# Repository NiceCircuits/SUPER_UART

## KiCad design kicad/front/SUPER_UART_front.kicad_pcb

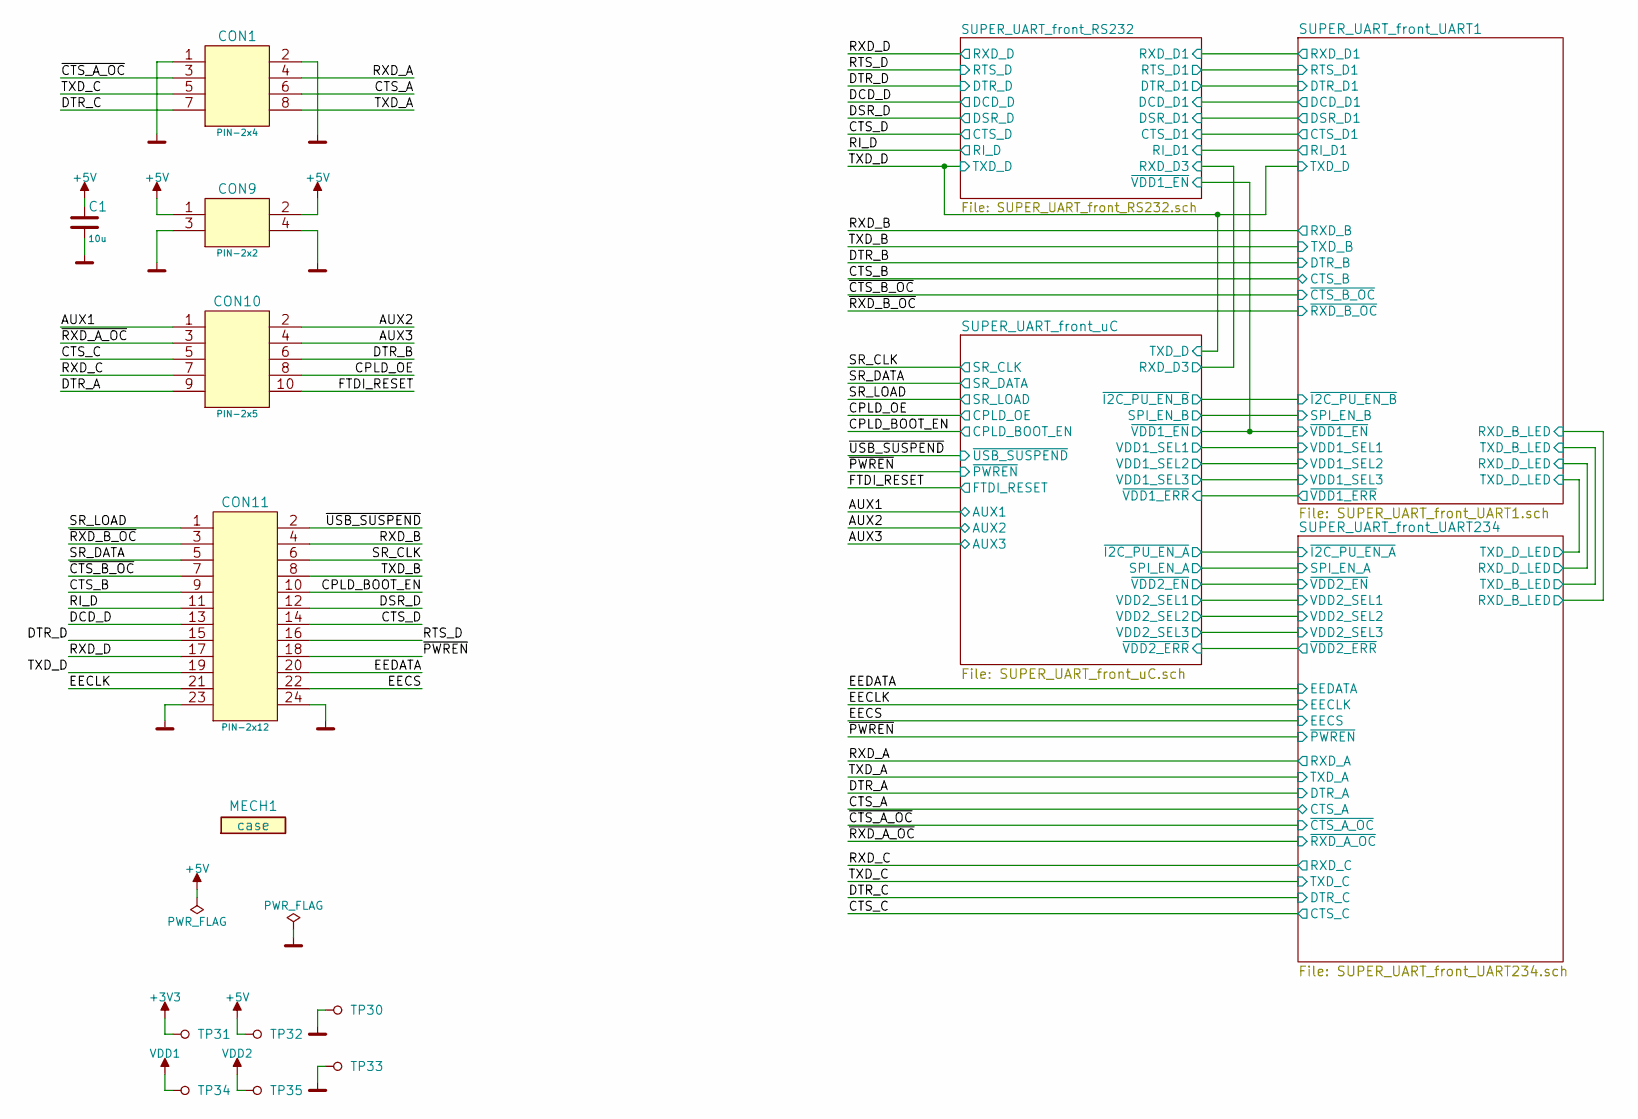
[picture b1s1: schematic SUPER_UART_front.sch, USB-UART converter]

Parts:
C1: 10u; 0805_N
CON1: PIN-2x4; PIN4x2SMD
CON9: PIN-2x2; PIN2x2SMD
CON10: PIN-2x5; PIN5x2SMD
CON11: PIN-2x12; PIN12x2SMD
MECH1: case; dummy
TP30, TP31, TP32, TP33, TP34, TP35: Testpoint; TP_1mm

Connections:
+3V3: TP31.1; also elsewhere on the board
+5V: C1.1, CON9.1, CON9.2, TP32.1; also elsewhere on the board
/AUX1: CON10.1; also elsewhere on the board
/AUX2: CON10.2; also elsewhere on the board
/AUX3: CON10.4; also elsewhere on the board
/CPLD_BOOT_EN: CON11.10; also elsewhere on the board
/CPLD_OE: CON10.8; also elsewhere on the board
/CTS_A: CON1.6; also elsewhere on the board
/CTS_B: CON11.9; also elsewhere on the board
/CTS_C: CON10.5; also elsewhere on the board
/CTS_D: CON11.14; also elsewhere on the board
/DCD_D: CON11.13; also elsewhere on the board
/DSR_D: CON11.12; also elsewhere on the board
/DTR_A: CON10.9; also elsewhere on the board
/DTR_B: CON10.6; also elsewhere on the board
/DTR_C: CON1.7; also elsewhere on the board
/DTR_D: CON11.15; also elsewhere on the board
/EECLK: CON11.21; also elsewhere on the board
/EECS: CON11.22; also elsewhere on the board
/EEDATA: CON11.20; also elsewhere on the board
/FTDI_RESET: CON10.10; also elsewhere on the board
/RI_D: CON11.11; also elsewhere on the board
/RTS_D: CON11.16; also elsewhere on the board
/RXD_A: CON1.4; also elsewhere on the board
/RXD_B: CON11.4; also elsewhere on the board
/RXD_C: CON10.7; also elsewhere on the board
/RXD_D: CON11.17; also elsewhere on the board
/SR_CLK: CON11.6; also elsewhere on the board
/SR_DATA: CON11.5; also elsewhere on the board
/SR_LOAD: CON11.1; also elsewhere on the board
/TXD_A: CON1.8; also elsewhere on the board
/TXD_B: CON11.8; also elsewhere on the board
/TXD_C: CON1.5; also elsewhere on the board
/TXD_D: CON11.19; also elsewhere on the board
/~CTS_A_OC: CON1.3; also elsewhere on the board
/~CTS_B_OC: CON11.7; also elsewhere on the board
/~PWREN: CON11.18; also elsewhere on the board
/~RXD_A_OC: CON10.3; also elsewhere on the board
/~RXD_B_OC: CON11.3; also elsewhere on the board
/~USB_SUSPEND: CON11.2; also elsewhere on the board
GND: C1.2, CON1.1, CON1.2, CON9.3, CON9.4, CON11.23, CON11.24, TP30.1, TP33.1; also elsewhere on the board
VDD1: TP34.1; also elsewhere on the board
VDD2: TP35.1; also elsewhere on the board

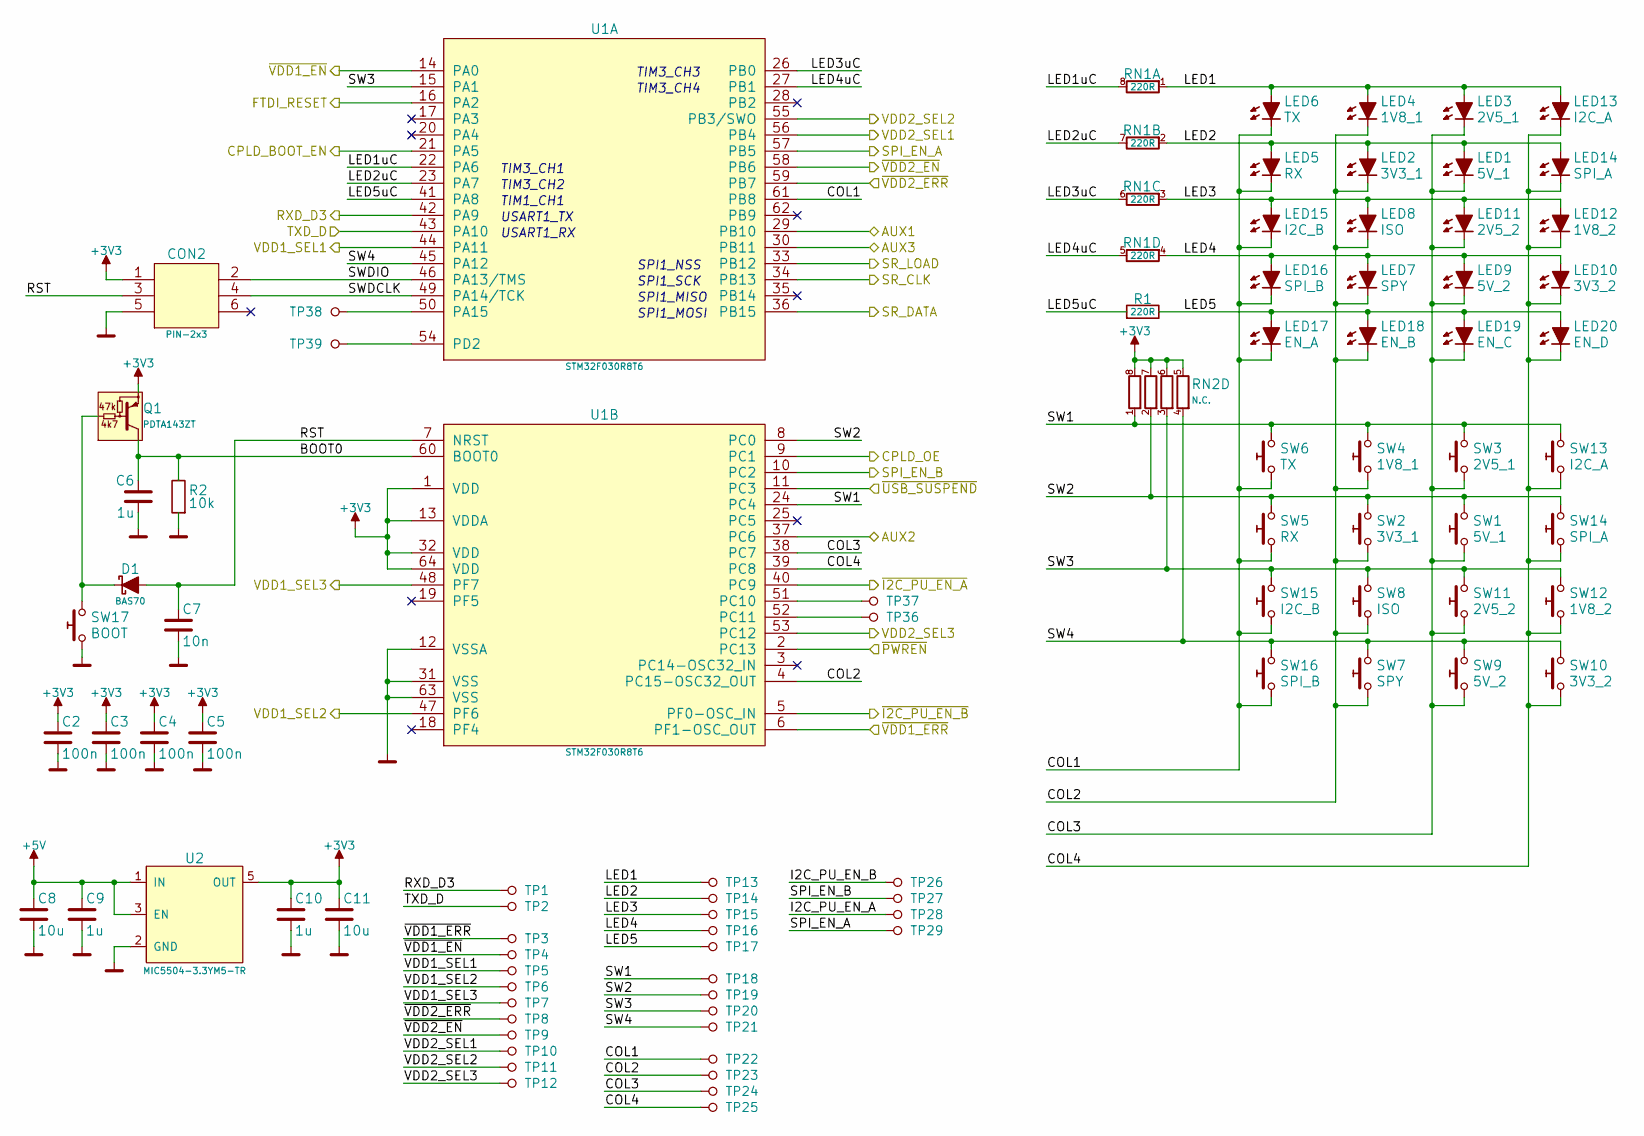
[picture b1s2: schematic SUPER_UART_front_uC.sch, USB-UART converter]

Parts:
C2, C3, C4, C5: 100n; 0603_N
C6, C9, C10: 1u; 0603_N
C7: 10n; 0603_N
C8, C11: 10u; 0805_N
CON2: PIN-2x3; PIN3x2SMD
D1: BAS70; SOT23-3_N
LED1: 5V_1; 0805D
LED2: 3V3_1; 0805D
LED3: 2V5_1; 0805D
LED4: 1V8_1; 0805D
LED5: RX; 0805D
LED6: TX; 0805D
LED7: SPY; 0805D
LED8: ISO; 0805D
LED9: 5V_2; 0805D
LED10: 3V3_2; 0805D
LED11: 2V5_2; 0805D
LED12: 1V8_2; 0805D
LED13: I2C_A; 0805D
LED14: SPI_A; 0805D
LED15: I2C_B; 0805D
LED16: SPI_B; 0805D
LED17: EN_A; 0805D
LED18: EN_B; 0805D
LED19: EN_C; 0805D
LED20: EN_D; 0805D
Q1: PDTA143ZT; SOT23-3_N
R1: 220R; 0603_R_N
R2: 10k; 0603_R_N
RN1: 220R; 4x0603_N
RN2: N.C.; 4x0603_N
SW1: 5V_1; TACTB-64K-F
SW2: 3V3_1; TACTB-64K-F
SW3: 2V5_1; TACTB-64K-F
SW4: 1V8_1; TACTB-64K-F
SW5: RX; TACTB-64K-F
SW6: TX; TACTB-64K-F
SW7: SPY; TACTB-64K-F
SW8: ISO; TACTB-64K-F
SW9: 5V_2; TACTB-64K-F
SW10: 3V3_2; TACTB-64K-F
SW11: 2V5_2; TACTB-64K-F
SW12: 1V8_2; TACTB-64K-F
SW13: I2C_A; TACTB-64K-F
SW14: SPI_A; TACTB-64K-F
SW15: I2C_B; TACTB-64K-F
SW16: SPI_B; TACTB-64K-F
SW17: BOOT; TACTB-64K-F
TP1, TP2, TP3, TP4, TP5, TP6, TP7, TP8, TP9, TP10, TP11, TP12, TP13, TP14, TP15, TP16, TP17, TP18, TP19, TP20, TP21, TP22, TP23, TP24, TP25, TP26, TP27, TP28, TP29, TP36, TP37, TP38, TP39: Testpoint; TP_1mm
U1: STM32F030R8T6; QFP-64-0.5_N
U2: MIC5504-3.3YM5-TR; SOT23-5_N

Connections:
+3V3: C2.1, C3.1, C4.1, C5.1, C10.1, C11.1, CON2.1, Q1.2 (E), RN2.5, RN2.6, RN2.7, RN2.8, U1.1 (VDD), U1.13 (VDDA), U1.32 (VDD), U1.64 (VDD), U2.5 (OUT); also elsewhere on the board
+5V: C8.1, C9.1, U2.1 (IN), U2.3 (EN); also elsewhere on the board
/AUX1: U1.29 (PB10); also elsewhere on the board
/AUX2: U1.37 (PC6); also elsewhere on the board
/AUX3: U1.30 (PB11); also elsewhere on the board
/CPLD_BOOT_EN: U1.21 (PA5); also elsewhere on the board
/CPLD_OE: U1.9 (PC1); also elsewhere on the board
/FTDI_RESET: U1.16 (PA2); also elsewhere on the board
/SR_CLK: U1.34 (PB13); also elsewhere on the board
/SR_DATA: U1.36 (PB15); also elsewhere on the board
/SR_LOAD: U1.33 (PB12); also elsewhere on the board
/SUPER_UART_front_RS232/RXD_D3: TP1.1, U1.42 (PA9); also elsewhere on the board
/SUPER_UART_front_RS232/~VDD1_EN: TP4.1, U1.14 (PA0); also elsewhere on the board
/SUPER_UART_front_UART1/I2C_PU_EN_B: TP26.1, U1.5 (PF0-OSC_IN); also elsewhere on the board
/SUPER_UART_front_UART1/SPI_EN_B: TP27.1, U1.10 (PC2); also elsewhere on the board
/SUPER_UART_front_UART1/VDD1_SEL1: TP5.1, U1.44 (PA11); also elsewhere on the board
/SUPER_UART_front_UART1/VDD1_SEL2: TP6.1, U1.47 (PF6); also elsewhere on the board
/SUPER_UART_front_UART1/VDD1_SEL3: TP7.1, U1.48 (PF7); also elsewhere on the board
/SUPER_UART_front_UART1/~VDD1_ERR: TP3.1, U1.6 (PF1-OSC_OUT); also elsewhere on the board
/SUPER_UART_front_UART234/I2C_PU_EN_A: TP28.1, U1.40 (PC9); also elsewhere on the board
/SUPER_UART_front_UART234/SPI_EN_A: TP29.1, U1.57 (PB5); also elsewhere on the board
/SUPER_UART_front_UART234/VDD2_SEL1: TP10.1, U1.56 (PB4); also elsewhere on the board
/SUPER_UART_front_UART234/VDD2_SEL2: TP11.1, U1.55 (PB3/SWO); also elsewhere on the board
/SUPER_UART_front_UART234/VDD2_SEL3: TP12.1, U1.53 (PC12); also elsewhere on the board
/SUPER_UART_front_UART234/~VDD2_EN: TP9.1, U1.58 (PB6); also elsewhere on the board
/SUPER_UART_front_UART234/~VDD2_ERR: TP8.1, U1.59 (PB7); also elsewhere on the board
/SUPER_UART_front_uC/BOOT0: C6.1, Q1.3 (C), R2.2, U1.60 (BOOT0)
/SUPER_UART_front_uC/COL1: LED5.1 (A), LED6.1 (A), LED15.1 (A), LED16.1 (A), LED17.1 (A), SW5.2, SW6.2, SW15.2, SW16.2, TP22.1, U1.61 (PB8)
/SUPER_UART_front_uC/COL2: LED2.1 (A), LED4.1 (A), LED7.1 (A), LED8.1 (A), LED18.1 (A), SW2.2, SW4.2, SW7.2, SW8.2, TP23.1, U1.4 (PC15-OSC32_OUT)
/SUPER_UART_front_uC/COL3: LED1.1 (A), LED3.1 (A), LED9.1 (A), LED11.1 (A), LED19.1 (A), SW1.2, SW3.2, SW9.2, SW11.2, TP24.1, U1.38 (PC7)
/SUPER_UART_front_uC/COL4: LED10.1 (A), LED12.1 (A), LED13.1 (A), LED14.1 (A), LED20.1 (A), SW10.2, SW12.2, SW13.2, SW14.2, TP25.1, U1.39 (PC8)
/SUPER_UART_front_uC/LED1: LED3.2 (C), LED4.2 (C), LED6.2 (C), LED13.2 (C), RN1.1, TP13.1
/SUPER_UART_front_uC/LED1uC: RN1.8, U1.22 (PA6)
/SUPER_UART_front_uC/LED2: LED1.2 (C), LED2.2 (C), LED5.2 (C), LED14.2 (C), RN1.2, TP14.1
/SUPER_UART_front_uC/LED2uC: RN1.7, U1.23 (PA7)
/SUPER_UART_front_uC/LED3: LED8.2 (C), LED11.2 (C), LED12.2 (C), LED15.2 (C), RN1.3, TP15.1
/SUPER_UART_front_uC/LED3uC: RN1.6, U1.26 (PB0)
/SUPER_UART_front_uC/LED4: LED7.2 (C), LED9.2 (C), LED10.2 (C), LED16.2 (C), RN1.4, TP16.1
/SUPER_UART_front_uC/LED4uC: RN1.5, U1.27 (PB1)
/SUPER_UART_front_uC/LED5: LED17.2 (C), LED18.2 (C), LED19.2 (C), LED20.2 (C), R1.2, TP17.1
/SUPER_UART_front_uC/LED5uC: R1.1, U1.41 (PA8)
/SUPER_UART_front_uC/RST: C7.1, CON2.3, D1.1 (C), U1.7 (NRST)
/SUPER_UART_front_uC/SW1: RN2.1, SW3.1, SW4.1, SW6.1, SW13.1, TP18.1, U1.24 (PC4)
/SUPER_UART_front_uC/SW2: RN2.2, SW1.1, SW2.1, SW5.1, SW14.1, TP19.1, U1.8 (PC0)
/SUPER_UART_front_uC/SW3: RN2.3, SW8.1, SW11.1, SW12.1, SW15.1, TP20.1, U1.15 (PA1)
/SUPER_UART_front_uC/SW4: RN2.4, SW7.1, SW9.1, SW10.1, SW16.1, TP21.1, U1.45 (PA12)
/SUPER_UART_front_uC/SWDCLK: CON2.4, U1.49 (PA14/TCK)
/SUPER_UART_front_uC/SWDIO: CON2.2, U1.46 (PA13/TMS)
/TXD_D: TP2.1, U1.43 (PA10); also elsewhere on the board
/~PWREN: U1.2 (PC13); also elsewhere on the board
/~USB_SUSPEND: U1.11 (PC3); also elsewhere on the board
GND: C2.2, C3.2, C4.2, C5.2, C6.2, C7.2, C8.2, C9.2, C10.2, C11.2, CON2.5, R2.1, SW17.2, U1.12 (VSSA), U1.31 (VSS), U1.63 (VSS), U2.2 (GND); also elsewhere on the board
unnamed: D1.3 (A), Q1.1 (B), SW17.1
unnamed: TP36.1, U1.52 (PC11)
unnamed: TP37.1, U1.51 (PC10)
unnamed: TP38.1, U1.50 (PA15)
unnamed: TP39.1, U1.54 (PD2)

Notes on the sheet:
USART1_TX
USART1_RX
TIM3_CH1
TIM3_CH2
TIM1_CH1
TIM3_CH3
TIM3_CH4
SPI1_NSS
SPI1_SCK
SPI1_MISO
SPI1_MOSI

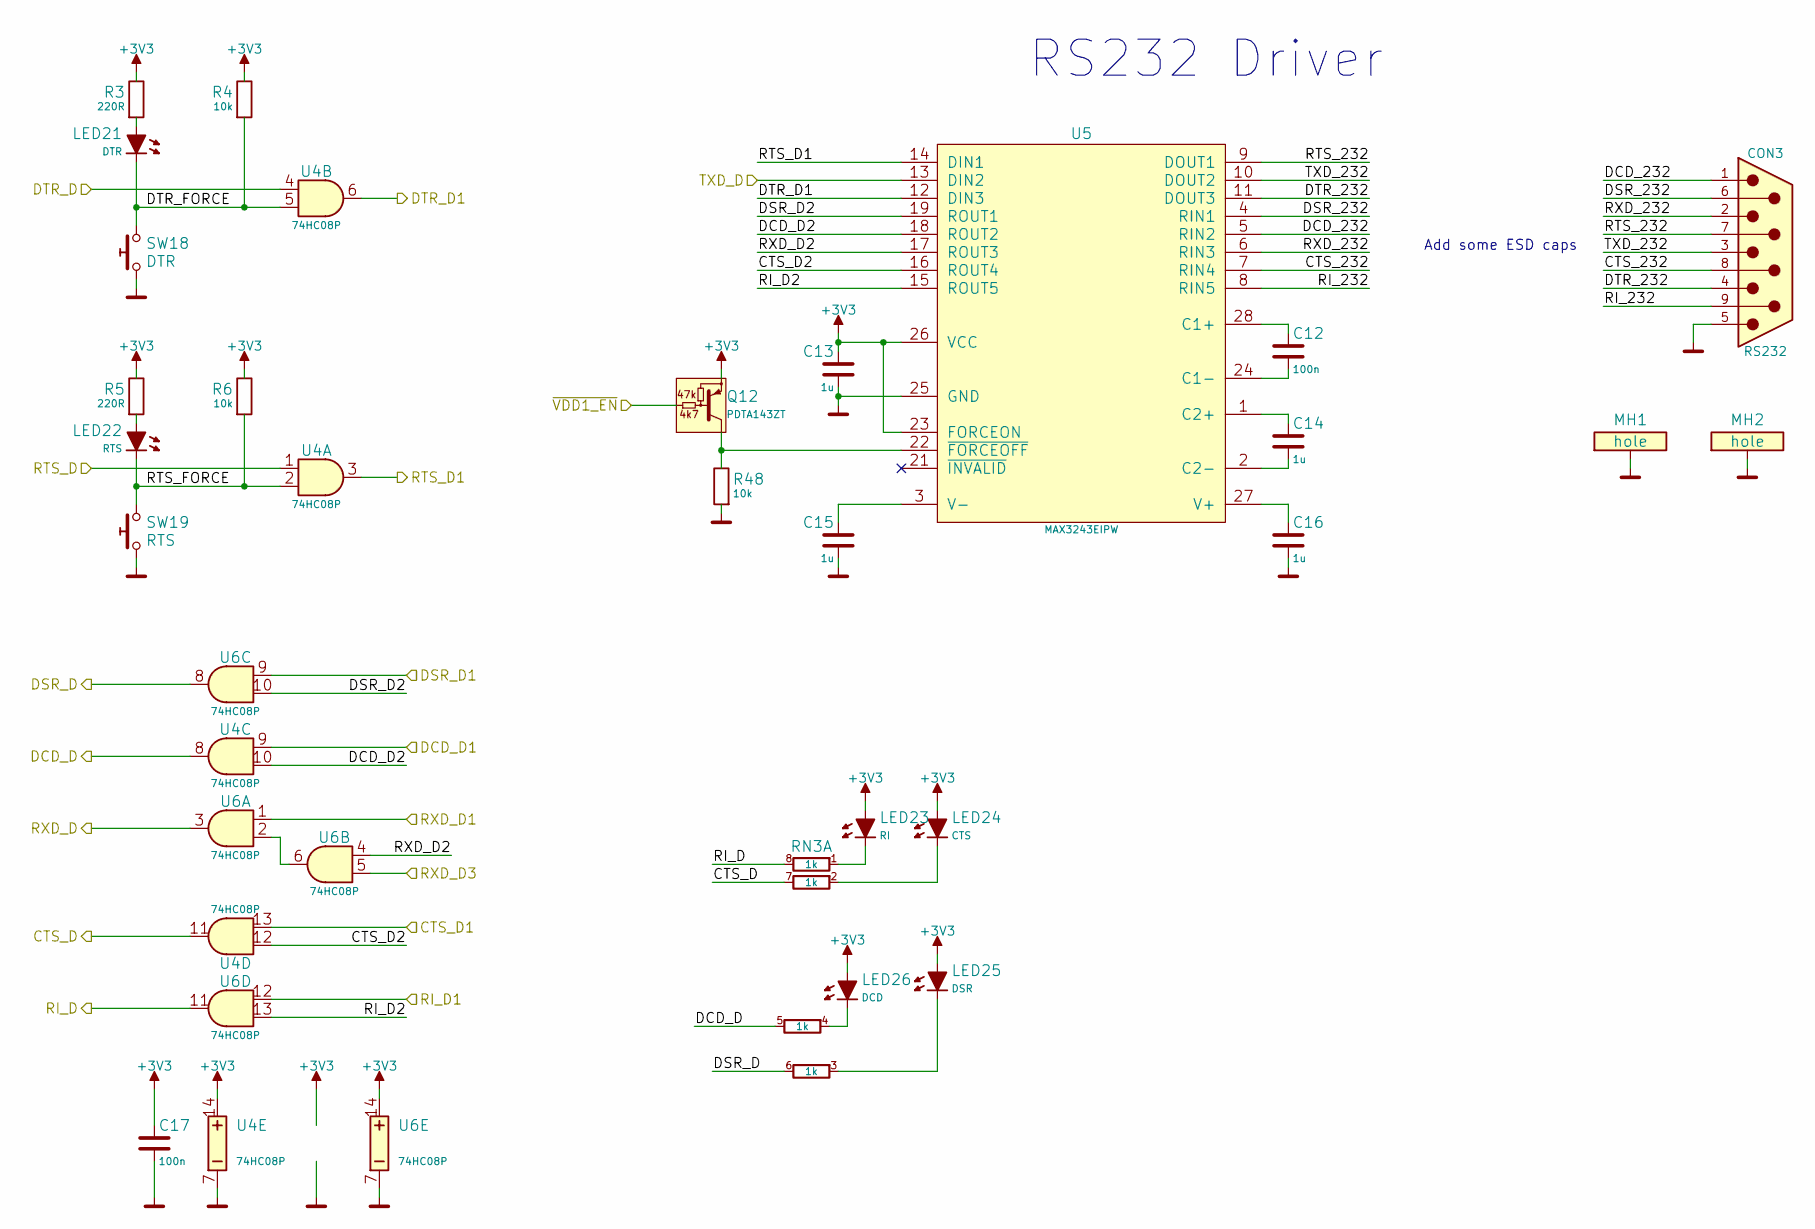
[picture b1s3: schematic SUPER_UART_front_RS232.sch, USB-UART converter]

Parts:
C12, C17: 100n; 0603_N
C13, C14, C15, C16: 1u; 0603_N
CON3: RS232; DB9MV
LED21: DTR; 0805D
LED22: RTS; 0805D
LED23: RI; 0805D
LED24: CTS; 0805D
LED25: DSR; 0805D
LED26: DCD; 0805D
MH1, MH2: hole; mounting_hole_3.2_7.5_plated
Q12: PDTA143ZT; SOT23-3_N
R3, R5: 220R; 0603_R_N
R4, R6, R48: 10k; 0603_R_N
RN3: 1k; 4x0603_N
SW18: DTR; TACTB-64K-F
SW19: RTS; TACTB-64K-F
U4, U6: 74HC08P; TSSOP-14_N
U5: MAX3243EIPW; TSSOP-28_N

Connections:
+3V3: C13.1, C17.1, LED23.2 (C), LED24.2 (C), LED25.2 (C), LED26.2 (C), Q12.2 (E), R3.2, R4.2, R5.2, R6.2, U4.14 (VCC), U5.23 (FORCEON), U5.26 (VCC), U6.14 (VCC); also elsewhere on the board
/CTS_D: RN3.7, U4.11 (OUT); also elsewhere on the board
/DCD_D: RN3.5, U4.8 (OUT); also elsewhere on the board
/DSR_D: RN3.6, U6.8 (OUT); also elsewhere on the board
/DTR_D: U4.4 (in1); also elsewhere on the board
/RI_D: RN3.8, U6.11 (OUT); also elsewhere on the board
/RTS_D: U4.1 (in1); also elsewhere on the board
/RXD_D: U6.3 (OUT); also elsewhere on the board
/SUPER_UART_front_RS232/CTS_232: CON3.8, U5.7 (RIN4)
/SUPER_UART_front_RS232/CTS_D1: U4.13 (in2); also elsewhere on the board
/SUPER_UART_front_RS232/CTS_D2: U4.12 (in1), U5.16 (ROUT4)
/SUPER_UART_front_RS232/DCD_232: CON3.1, U5.5 (RIN2)
/SUPER_UART_front_RS232/DCD_D1: U4.9 (in1); also elsewhere on the board
/SUPER_UART_front_RS232/DCD_D2: U4.10 (in2), U5.18 (ROUT2)
/SUPER_UART_front_RS232/DSR_232: CON3.6, U5.4 (RIN1)
/SUPER_UART_front_RS232/DSR_D1: U6.9 (in1); also elsewhere on the board
/SUPER_UART_front_RS232/DSR_D2: U5.19 (ROUT1), U6.10 (in2)
/SUPER_UART_front_RS232/DTR_232: CON3.4, U5.11 (DOUT3)
/SUPER_UART_front_RS232/DTR_D1: U4.6 (OUT), U5.12 (DIN3); also elsewhere on the board
/SUPER_UART_front_RS232/DTR_FORCE: LED21.1 (A), R4.1, SW18.1, U4.5 (in2)
/SUPER_UART_front_RS232/RI_232: CON3.9, U5.8 (RIN5)
/SUPER_UART_front_RS232/RI_D1: U6.12 (in1); also elsewhere on the board
/SUPER_UART_front_RS232/RI_D2: U5.15 (ROUT5), U6.13 (in2)
/SUPER_UART_front_RS232/RTS_232: CON3.7, U5.9 (DOUT1)
/SUPER_UART_front_RS232/RTS_D1: U4.3 (OUT), U5.14 (DIN1); also elsewhere on the board
/SUPER_UART_front_RS232/RTS_FORCE: LED22.1 (A), R6.1, SW19.1, U4.2 (in2)
/SUPER_UART_front_RS232/RXD_232: CON3.2, U5.6 (RIN3)
/SUPER_UART_front_RS232/RXD_D1: U6.1 (in1); also elsewhere on the board
/SUPER_UART_front_RS232/RXD_D2: U5.17 (ROUT3), U6.4 (in1)
/SUPER_UART_front_RS232/RXD_D3: U6.5 (in2); also elsewhere on the board
/SUPER_UART_front_RS232/TXD_232: CON3.3, U5.10 (DOUT2)
/SUPER_UART_front_RS232/~VDD1_EN: Q12.1 (B); also elsewhere on the board
/TXD_D: U5.13 (DIN2); also elsewhere on the board
GND: C13.2, C15.2, C16.2, C17.2, CON3.5, MH1.1, MH2.1, R48.1, SW18.2, SW19.2, U4.7 (GND), U5.25 (GND), U6.7 (GND); also elsewhere on the board
unnamed: C12.1, U5.28 (C1+)
unnamed: C12.2, U5.24 (C1-)
unnamed: C14.1, U5.1 (C2+)
unnamed: C14.2, U5.2 (C2-)
unnamed: C15.1, U5.3 (V-)
unnamed: C16.1, U5.27 (V+)
unnamed: LED21.2 (C), R3.1
unnamed: LED22.2 (C), R5.1
unnamed: LED23.1 (A), RN3.1
unnamed: LED24.1 (A), RN3.2
unnamed: LED25.1 (A), RN3.3
unnamed: LED26.1 (A), RN3.4
unnamed: Q12.3 (C), R48.2, U5.22 (~FORCEOFF)
unnamed: U6.2 (in2), U6.6 (OUT)

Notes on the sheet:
RS232 Driver
Add some ESD caps

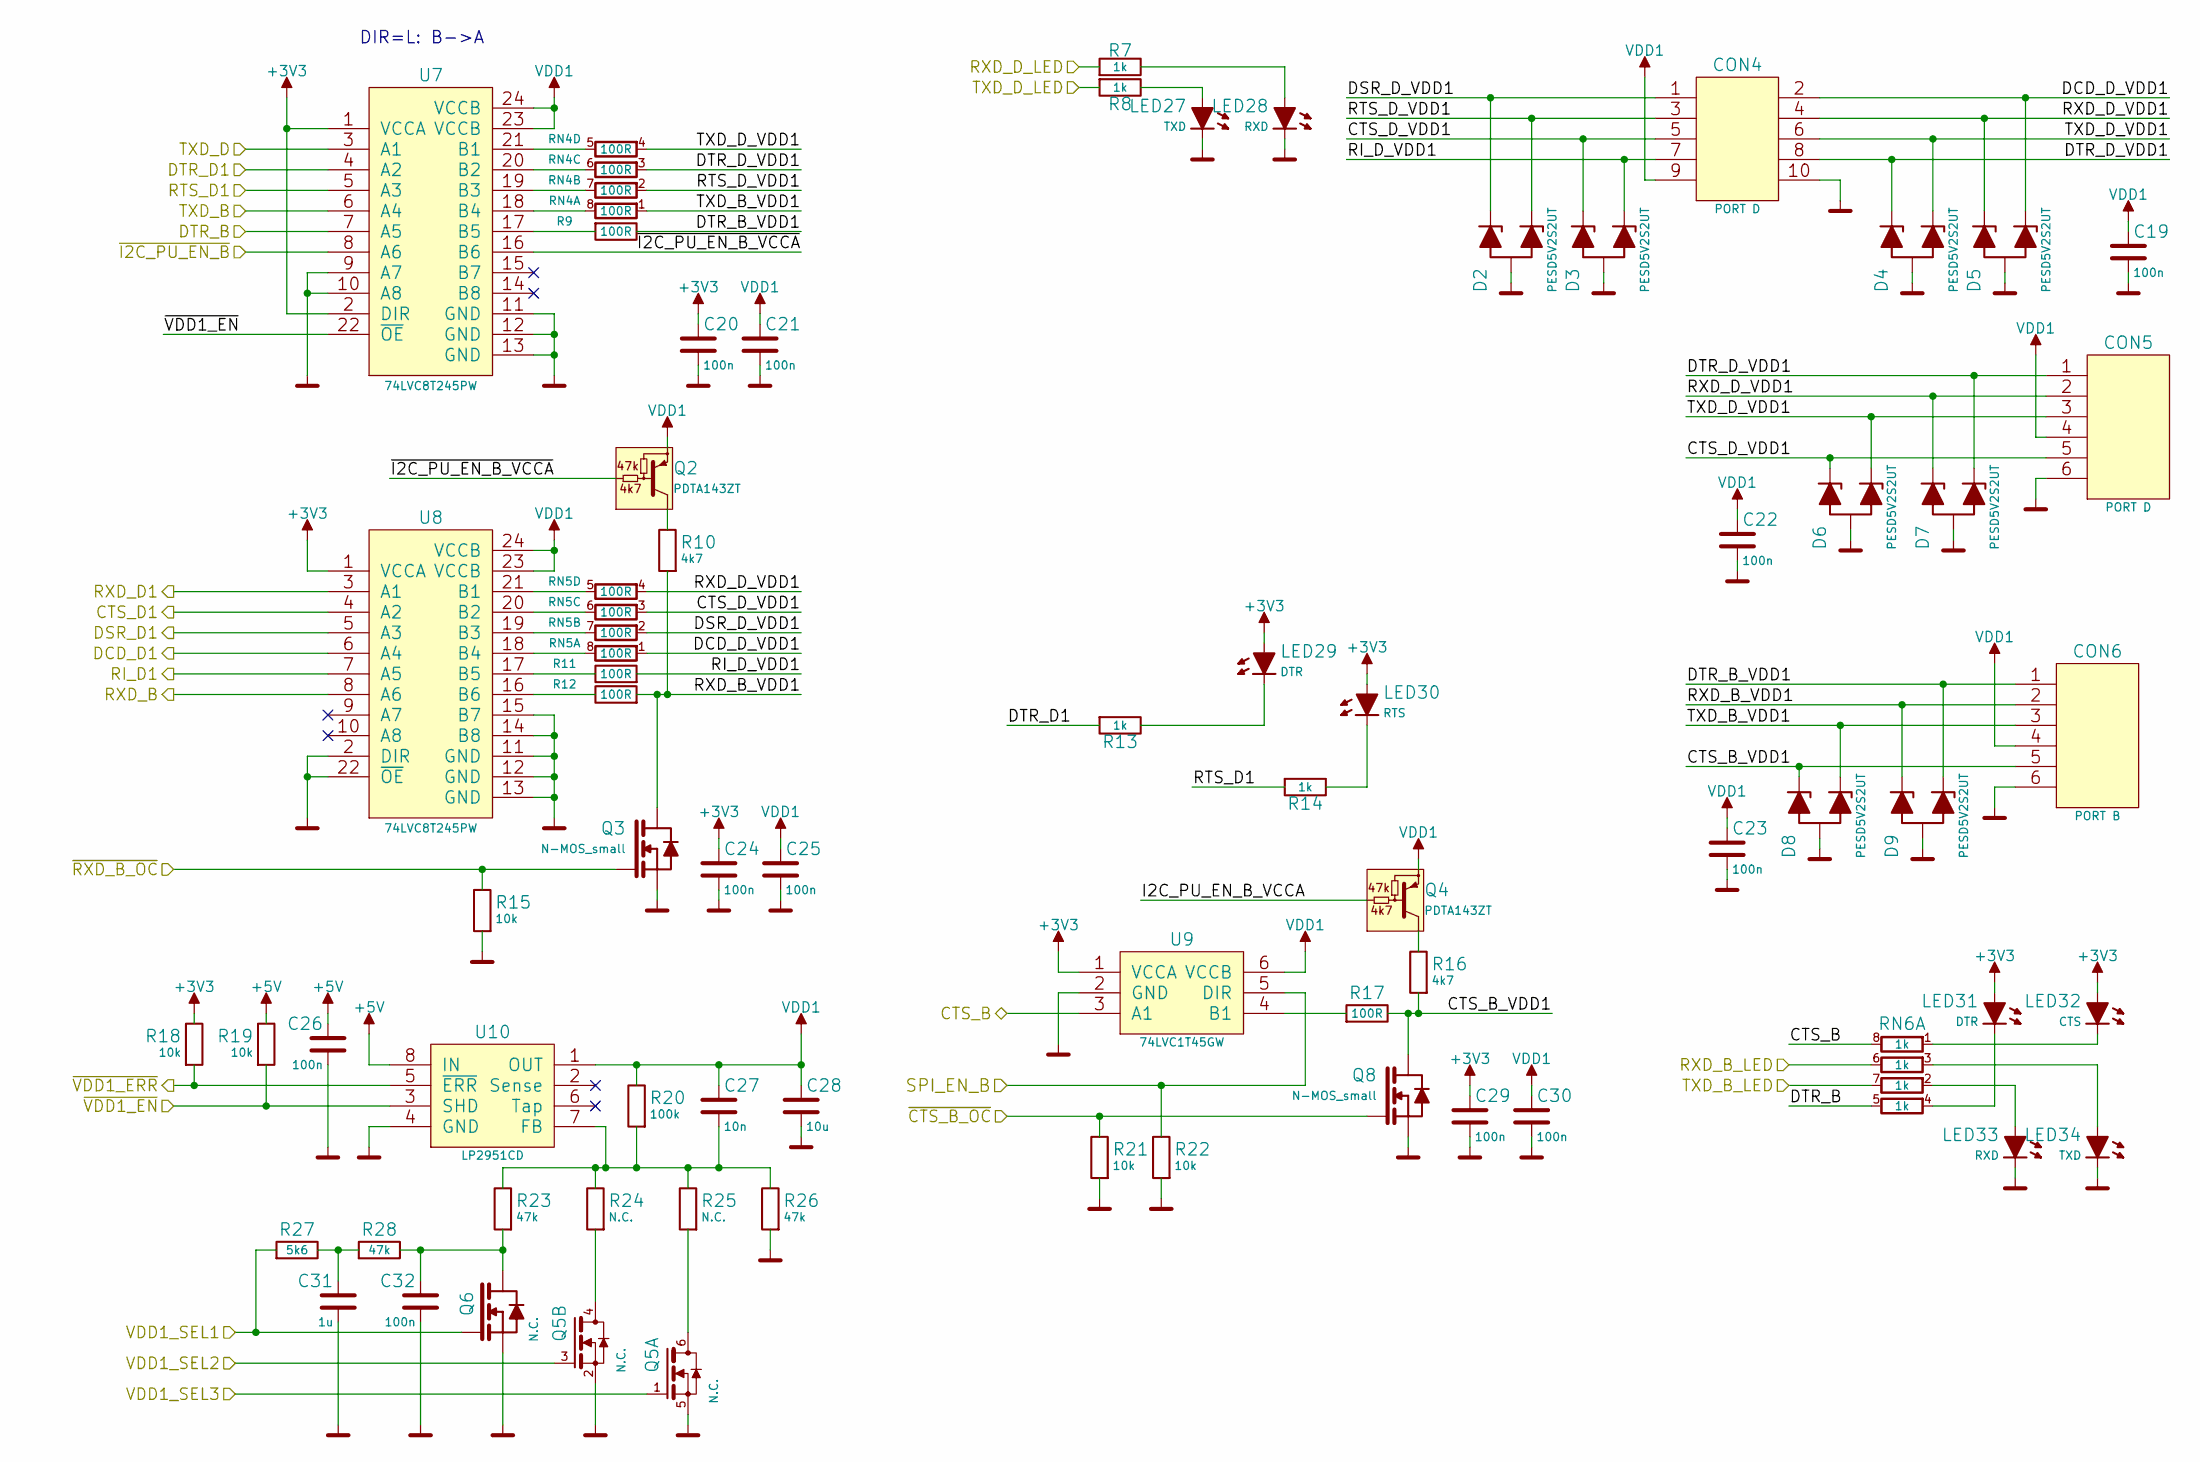
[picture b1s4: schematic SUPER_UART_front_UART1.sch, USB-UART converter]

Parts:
C19, C20, C21, C22, C23, C24, C25, C26, C29, C30, C32: 100n; 0603_N
C27: 10n; 0603_N
C28: 10u; 0805_N
C31: 1u; 0603_N
CON4: PORT D; IDC10
CON5: PORT D; NIGINI_NCDW-06
CON6: PORT B; NIGINI_NCDW-06
D2, D3, D4, D5, D6, D7, D8, D9: PESD5V2S2UT; SOT23-3_N
LED27, LED34: TXD; 0805D
LED28, LED33: RXD; 0805D
LED29, LED31: DTR; 0805D
LED30: RTS; 0805D
LED32: CTS; 0805D
Q2, Q4: PDTA143ZT; SOT23-3_N
Q3, Q8: N-MOS_small; SOT23-3_N
Q5: N.C.; SC70-6_N
Q6: N.C.; SOT23-3_N
R7, R8, R13, R14: 1k; 0603_R_N
R9, R11, R12, R17: 100R; 0603_R_N
R10, R16: 4k7; 0603_R_N
R15, R18, R19, R21, R22: 10k; 0603_R_N
R20: 100k; 0603_R_N
R23, R26, R28: 47k; 0603_R_N
R24, R25: N.C.; 0603_R_N
R27: 5k6; 0603_R_N
RN4, RN5: 100R; 4x0603_N
RN6: 1k; 4x0603_N
U7, U8: 74LVC8T245PW; TI_TSSOP-24_N
U9: 74LVC1T45GW; SC70-6_N
U10: LP2951CD; SOIC-8_N

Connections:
+3V3: C20.1, C24.1, C29.1, LED29.2 (C), LED30.2 (C), LED31.2 (C), LED32.2 (C), R18.2, U7.1 (VCCA), U7.2 (DIR), U8.1 (VCCA), U9.1 (VCCA); also elsewhere on the board
+5V: C26.1, R19.2, U10.8 (IN); also elsewhere on the board
/CTS_B: RN6.8, U9.3 (A1); also elsewhere on the board
/DTR_B: RN6.5, U7.7 (A5); also elsewhere on the board
/RXD_B: U8.8 (A6); also elsewhere on the board
/SUPER_UART_front_RS232/CTS_D1: U8.4 (A2); also elsewhere on the board
/SUPER_UART_front_RS232/DCD_D1: U8.6 (A4); also elsewhere on the board
/SUPER_UART_front_RS232/DSR_D1: U8.5 (A3); also elsewhere on the board
/SUPER_UART_front_RS232/DTR_D1: R13.1, U7.4 (A2); also elsewhere on the board
/SUPER_UART_front_RS232/RI_D1: U8.7 (A5); also elsewhere on the board
/SUPER_UART_front_RS232/RTS_D1: R14.1, U7.5 (A3); also elsewhere on the board
/SUPER_UART_front_RS232/RXD_D1: U8.3 (A1); also elsewhere on the board
/SUPER_UART_front_RS232/~VDD1_EN: R19.1, U7.22 (~OE), U10.3 (SHD); also elsewhere on the board
/SUPER_UART_front_UART1/CTS_B_VDD1: CON6.5, D8.1 (C1), Q8.3 (D), R16.1, R17.2
/SUPER_UART_front_UART1/CTS_D_VDD1: CON4.5, CON5.5, D3.1 (C1), D6.1 (C1), RN5.3
/SUPER_UART_front_UART1/DCD_D_VDD1: CON4.2, D5.2 (C2), RN5.1
/SUPER_UART_front_UART1/DSR_D_VDD1: CON4.1, D2.1 (C1), RN5.2
/SUPER_UART_front_UART1/DTR_B_VDD1: CON6.1, D9.2 (C2), R9.2
/SUPER_UART_front_UART1/DTR_D_VDD1: CON4.8, CON5.1, D4.1 (C1), D7.2 (C2), RN4.3
/SUPER_UART_front_UART1/I2C_PU_EN_B: U7.8 (A6); also elsewhere on the board
/SUPER_UART_front_UART1/RI_D_VDD1: CON4.7, D3.2 (C2), R11.1
/SUPER_UART_front_UART1/RTS_D_VDD1: CON4.3, D2.2 (C2), RN4.2
/SUPER_UART_front_UART1/RXD_B_LED: RN6.6; also elsewhere on the board
/SUPER_UART_front_UART1/RXD_B_VDD1: CON6.2, D9.1 (C1), Q3.3 (D), R10.1, R12.1
/SUPER_UART_front_UART1/RXD_D_LED: R7.1; also elsewhere on the board
/SUPER_UART_front_UART1/RXD_D_VDD1: CON4.4, CON5.2, D5.1 (C1), D7.1 (C1), RN5.4
/SUPER_UART_front_UART1/SPI_EN_B: R22.2, U9.5 (DIR); also elsewhere on the board
/SUPER_UART_front_UART1/TXD_B_LED: RN6.7; also elsewhere on the board
/SUPER_UART_front_UART1/TXD_B_VDD1: CON6.3, D8.2 (C2), RN4.1
/SUPER_UART_front_UART1/TXD_D_LED: R8.1; also elsewhere on the board
/SUPER_UART_front_UART1/TXD_D_VDD1: CON4.6, CON5.3, D4.2 (C2), D6.2 (C2), RN4.4
/SUPER_UART_front_UART1/VDD1_SEL1: Q6.1 (G), R27.1; also elsewhere on the board
/SUPER_UART_front_UART1/VDD1_SEL2: Q5.3 (G); also elsewhere on the board
/SUPER_UART_front_UART1/VDD1_SEL3: Q5.1 (G); also elsewhere on the board
/SUPER_UART_front_UART1/~VDD1_ERR: R18.1, U10.5 (~ERR); also elsewhere on the board
/TXD_B: U7.6 (A4); also elsewhere on the board
/TXD_D: U7.3 (A1); also elsewhere on the board
/~CTS_B_OC: Q8.1 (G), R21.2; also elsewhere on the board
/~RXD_B_OC: Q3.1 (G), R15.2; also elsewhere on the board
GND: C19.2, C20.2, C21.2, C22.2, C23.2, C24.2, C25.2, C26.2, C28.2, C29.2, C30.2, C31.2, C32.2, CON4.10, CON5.6, CON6.6, D2.3 (A), D3.3 (A), D4.3 (A), D5.3 (A), D6.3 (A), D7.3 (A), D8.3 (A), D9.3 (A), LED27.1 (A), LED28.1 (A), LED33.1 (A), LED34.1 (A), Q3.2 (S), Q5.2 (S), Q5.5 (S), Q6.2 (S), Q8.2 (S), R15.1, R21.1, R22.1, R26.1, U7.9 (A7), U7.10 (A8), U7.11 (GND), U7.12 (GND), U7.13 (GND), U8.2 (DIR), U8.11 (GND), U8.12 (GND), U8.13 (GND), U8.14 (B8), U8.15 (B7), U8.22 (~OE), U9.2 (GND), U10.4 (GND); also elsewhere on the board
unnamed: C27.2, R20.1, R23.2, R24.2, R25.2, R26.2, U10.7 (FB)
unnamed: C31.1, R27.2, R28.1
unnamed: C32.1, Q6.3 (D), R23.1, R28.2
unnamed: LED27.2 (C), R8.2
unnamed: LED28.2 (C), R7.2
unnamed: LED29.1 (A), R13.2
unnamed: LED30.1 (A), R14.2
unnamed: LED31.1 (A), RN6.4
unnamed: LED32.1 (A), RN6.1
unnamed: LED33.2 (C), RN6.2
unnamed: LED34.2 (C), RN6.3
unnamed: Q2.3 (C), R10.2
unnamed: Q4.3 (C), R16.2
unnamed: Q5.4 (D), R24.1
unnamed: Q5.6 (D), R25.1
unnamed: R9.1, U7.17 (B5)
unnamed: R11.2, U8.17 (B5)
unnamed: R12.2, U8.16 (B6)
unnamed: R17.1, U9.4 (B1)
unnamed: RN4.5, U7.21 (B1)
unnamed: RN4.6, U7.20 (B2)
unnamed: RN4.7, U7.19 (B3)
unnamed: RN4.8, U7.18 (B4)
unnamed: RN5.5, U8.21 (B1)
unnamed: RN5.6, U8.20 (B2)
unnamed: RN5.7, U8.19 (B3)
unnamed: RN5.8, U8.18 (B4)
VDD1: C19.1, C21.1, C22.1, C23.1, C25.1, C27.1, C28.1, C30.1, CON4.9, CON5.4, CON6.4, Q2.2 (E), Q4.2 (E), R20.2, U7.23 (VCCB), U7.24 (VCCB), U8.23 (VCCB), U8.24 (VCCB), U9.6 (VCCB), U10.1 (OUT); also elsewhere on the board

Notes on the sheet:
DIR=L: B->A
